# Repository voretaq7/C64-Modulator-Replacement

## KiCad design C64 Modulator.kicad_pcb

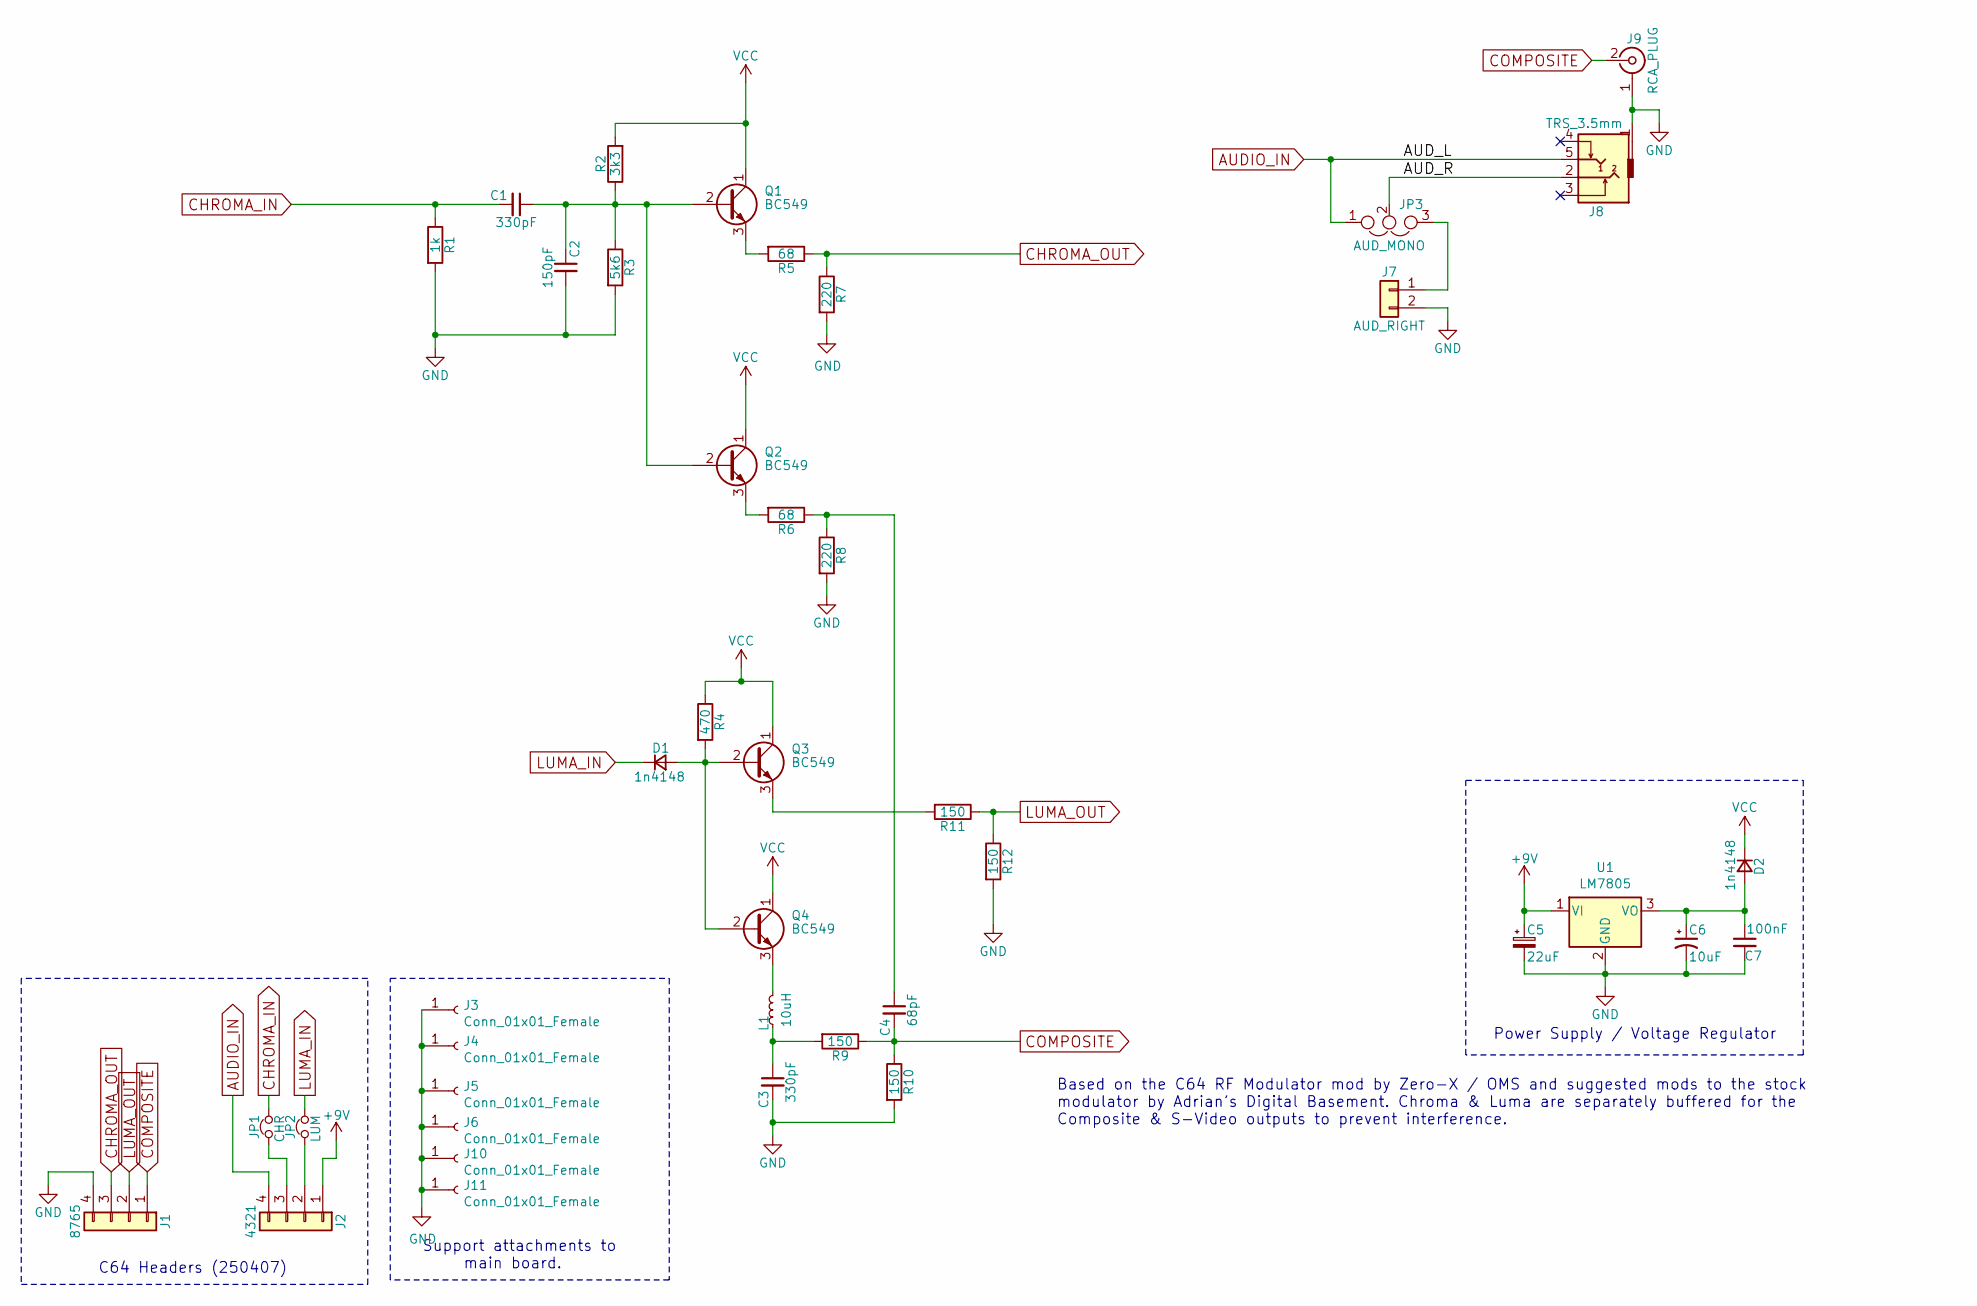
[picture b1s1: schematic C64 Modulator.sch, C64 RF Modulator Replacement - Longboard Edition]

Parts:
C1, C3: 330pF; C_Disc_D4.7mm_W2.5mm_P5.00mm
C2: 150pF; C_Disc_D4.7mm_W2.5mm_P5.00mm
C4: 68pF; C_Disc_D4.7mm_W2.5mm_P5.00mm
C5: 22uF; CP_Radial_D5.0mm_P2.50mm
C6: 10uF; CP_Radial_D5.0mm_P2.50mm
C7: 100nF; C_Disc_D4.7mm_W2.5mm_P5.00mm
D1, D2: 1n4148; D_DO-35_SOD27_P7.62mm_Horizontal
J1: 8765; Pin_Header_Straight_1x04_Pitch2.54mm
J2: 4321; Pin_Header_Straight_1x04_Pitch2.54mm
J3, J4, J5, J6, J10, J11: Conn_01x01_Female; PinHeader_1x01_P2.54mm_Vertical
J7: AUD_RIGHT; PinHeader_1x02_P2.54mm_Vertical
J8: TRS_3.5mm; Tayda_3.5mm_stereo_TRS_jack_A-853
J9: RCA_PLUG; rca_yellow
JP1: CHR; PinHeader_1x02_P2.54mm_Vertical
JP2: LUM; PinHeader_1x02_P2.54mm_Vertical
JP3: AUD_MONO; Pin_Header_Straight_1x03_Pitch2.54mm
L1: 10uH; L_Axial_L6.6mm_D2.7mm_P10.16mm_Horizontal_Vishay_IM-2
Q1, Q2, Q3, Q4: BC549; TO-92_Inline
R1: 1k; R_Axial_DIN0207_L6.3mm_D2.5mm_P10.16mm_Horizontal
R2: 3k3; R_Axial_DIN0207_L6.3mm_D2.5mm_P10.16mm_Horizontal
R3: 5k6; R_Axial_DIN0207_L6.3mm_D2.5mm_P10.16mm_Horizontal
R4: 470; R_Axial_DIN0207_L6.3mm_D2.5mm_P10.16mm_Horizontal
R5, R6: 68; R_Axial_DIN0207_L6.3mm_D2.5mm_P10.16mm_Horizontal
R7, R8: 220; R_Axial_DIN0207_L6.3mm_D2.5mm_P10.16mm_Horizontal
R9, R10, R11, R12: 150; R_Axial_DIN0207_L6.3mm_D2.5mm_P10.16mm_Horizontal
U1: LM7805; TO-220-3_Horizontal_TabDown

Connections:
+9V: C5.1, J2.1, U1.1 (VI)
/AUD_R: J8.2, JP3.2
AUDIO_IN: J2.4, J8.5, JP3.1
CHROMA_IN: C1.2, JP1.1, R1.1
CHROMA_OUT: J1.3, R5.1, R7.1
COMPOSITE: C4.2, J1.1, J9.2 (In), R9.1, R10.1
GND: C2.2, C3.2, C5.2, C6.2, C7.2, J1.4, J3.1, J4.1, J5.1, J6.1, J7.2, J8.1, J9.1 (Ext), J10.1, J11.1, R1.2, R3.2, R7.2, R8.2, R10.2, R12.2, U1.2 (GND)
LUMA_IN: D1.1 (K), JP2.1
LUMA_OUT: J1.2, R11.1, R12.1
unnamed: C1.1, C2.1, Q1.2 (B), Q2.2 (B), R2.1, R3.1
unnamed: C3.1, L1.1, R9.2
unnamed: C4.1, R6.1, R8.1
unnamed: C6.1, C7.1, D2.2 (A), U1.3 (VO)
unnamed: D1.2 (A), Q3.2 (B), Q4.2 (B), R4.2
unnamed: J2.2, JP2.2
unnamed: J2.3, JP1.2
unnamed: J7.1, JP3.3
unnamed: L1.2, Q4.3 (E)
unnamed: Q1.3 (E), R5.2
unnamed: Q2.3 (E), R6.2
unnamed: Q3.3 (E), R11.2
VCC: D2.1 (K), Q1.1 (C), Q2.1 (C), Q3.1 (C), Q4.1 (C), R2.2, R4.1

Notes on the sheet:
Based on the C64 RF Modulator mod by Zero-X / OMS and suggested mods to the stock modulator by Adrian’s Digital Basement. Chroma & Luma are separately buffered for the Composite & S-Video outputs to prevent interference.
Power Supply / Voltage Regulator
C64 Headers (250407)
Support attachments to main board.

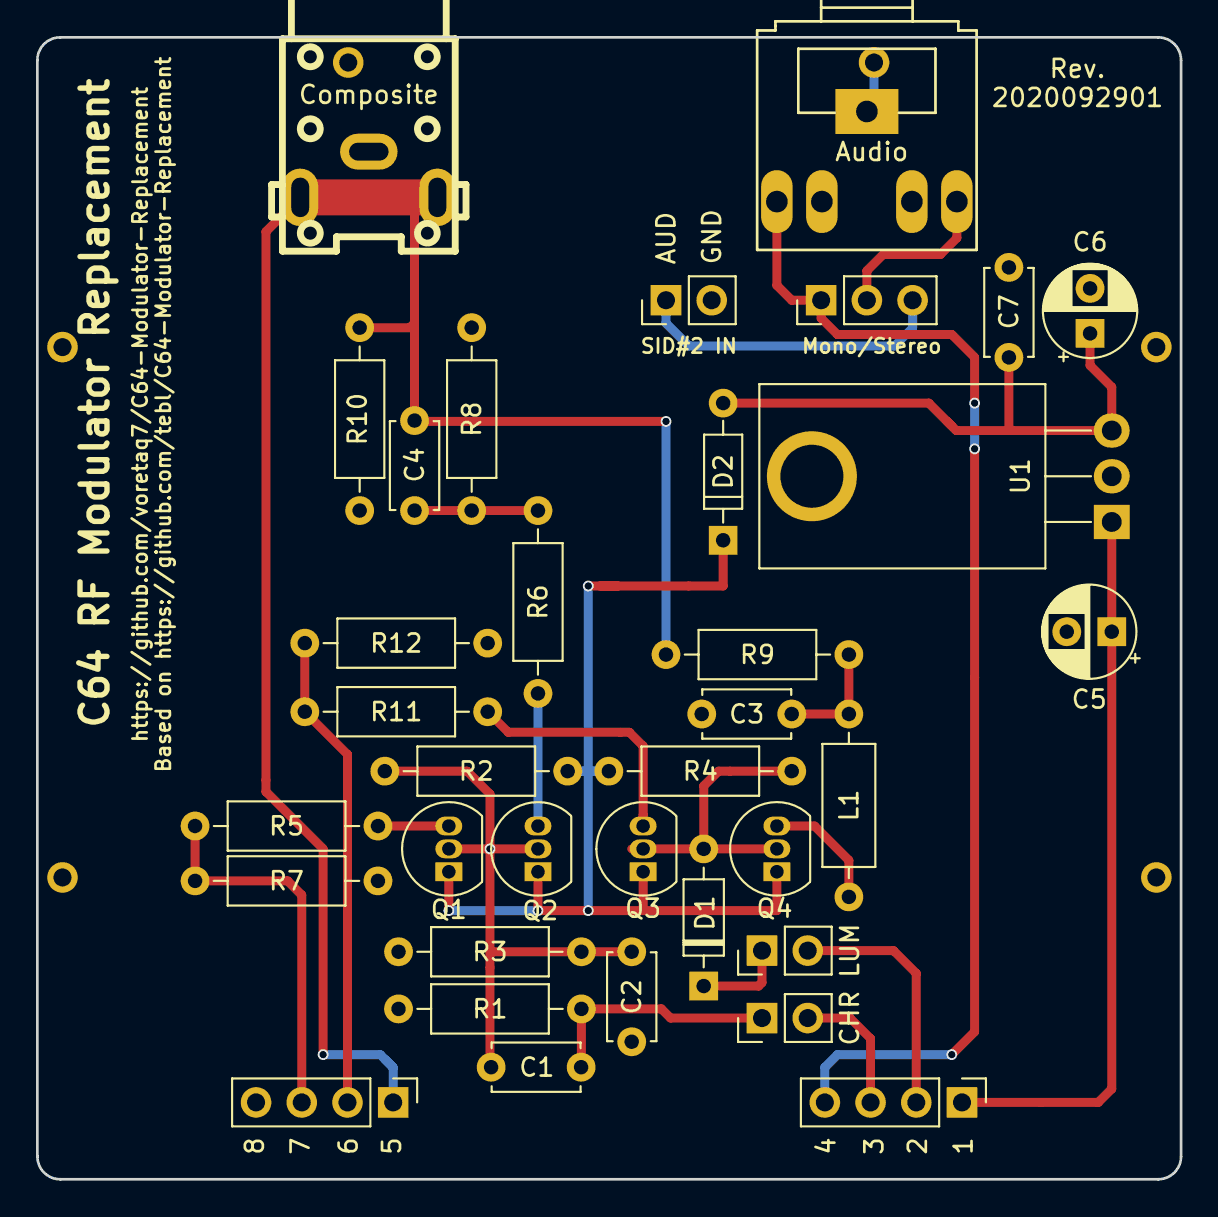
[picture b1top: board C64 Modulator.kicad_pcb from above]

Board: 2 copper layers, 63.5 x 63.4 mm, 41 parts (0 on the bottom side), 22 nets.

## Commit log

2020-09-29 Cleaned up library for new KiCad & started splitting Chroma/Luma/Comp
2020-09-29 Completed double-buffering Chroma/Luma split & library cleanup
2020-09-30 Minor PCB cleanup - Move Composite signal to top layer.
2020-09-30 Clean up courtyards so they don't overlap.
2020-10-06 Re-Add mounting point supports to main board (ground pins)
2021-03-10 Add mounting supports under RCA & TRS jack.
